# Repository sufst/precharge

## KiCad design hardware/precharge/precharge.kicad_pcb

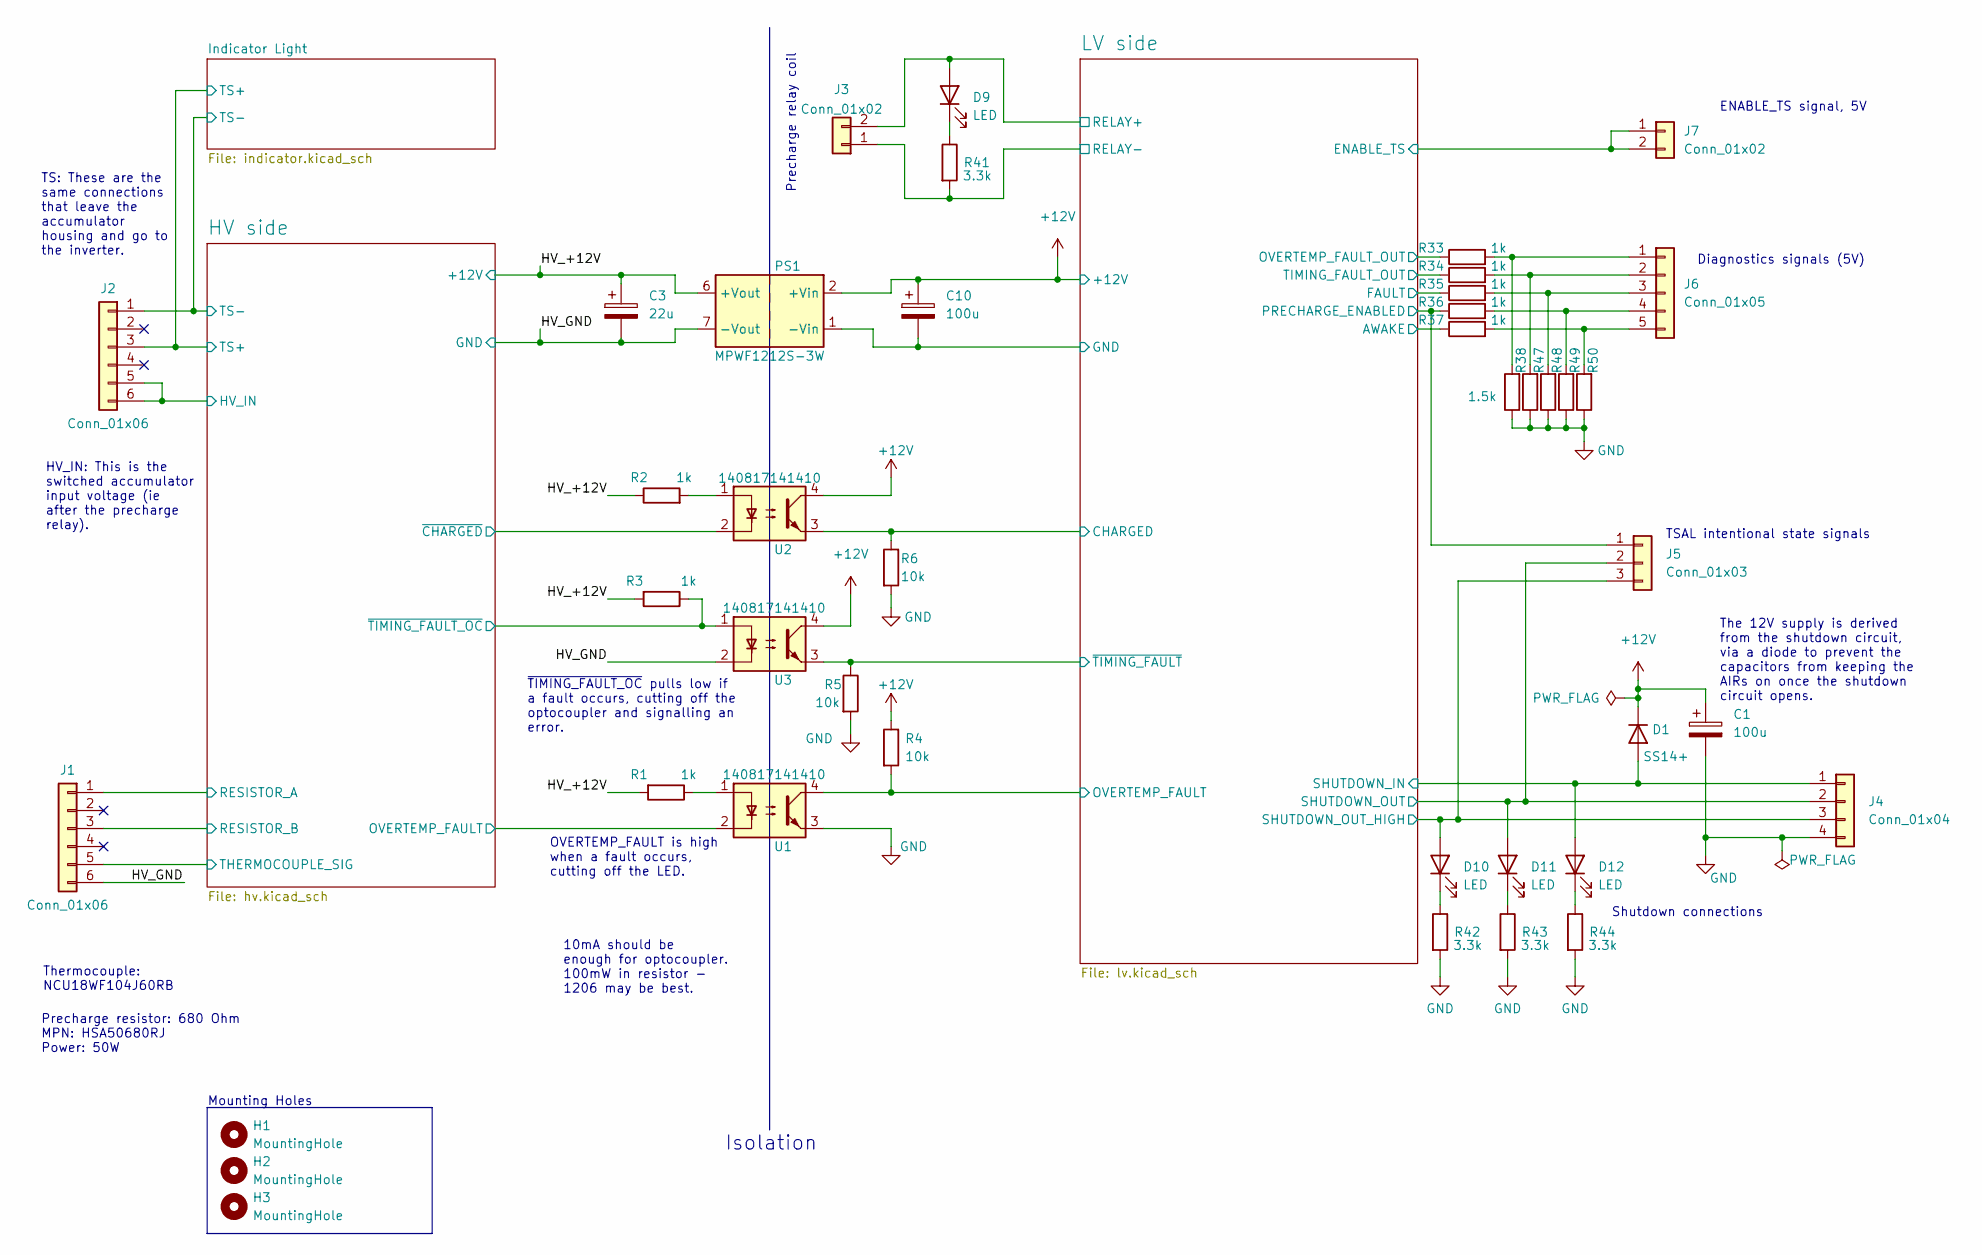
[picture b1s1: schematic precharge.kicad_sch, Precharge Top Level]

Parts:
C1, C10: 100u; CP_Radial_D6.3mm_P2.50mm
C3: 22u; CP_Radial_D8.0mm_P3.50mm
D1: SS14+; D_SMA
D9, D10, D11, D12: LED; LED_0603_1608Metric
H1, H2, H3: MountingHole; MountingHole_3.2mm_M3
J1, J2: Conn_01x06; Molex_Micro-Fit_3.0_43650-0600_1x06_P3.00mm_Horizontal
J3, J7: Conn_01x02; Molex_Micro-Fit_3.0_43650-0200_1x02_P3.00mm_Horizontal
J4: Conn_01x04; Molex_Micro-Fit_3.0_43650-0400_1x04_P3.00mm_Horizontal
J5: Conn_01x03; Molex_Micro-Fit_3.0_43650-0300_1x03_P3.00mm_Horizontal
J6: Conn_01x05; Molex_Micro-Fit_3.0_43650-0500_1x05_P3.00mm_Horizontal
PS1: MPWF1212S-3W
R1, R2, R3: 1k; R_1206_3216Metric
R4, R5, R6: 10k; R_0603_1608Metric
R33, R34, R35, R36, R37: 1k; R_0603_1608Metric
R38, R47, R48, R49, R50: 1.5k; R_0603_1608Metric
R41, R42, R43, R44: 3.3k; R_0603_1608Metric
U1, U2, U3: 140817141410; DIP-4_W10.16mm

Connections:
+12V: C1.1, C10.1, D1.1 (K), PS1.2 (+Vin), R4.1, U2.4, U3.4; also elsewhere on the board
/HV side/HV_IN: J2.5, J2.6; also elsewhere on the board
/HV side/OVERTEMP_FAULT: U1.2; also elsewhere on the board
/HV side/RESISTOR_A: J1.1; also elsewhere on the board
/HV side/RESISTOR_B: J1.3, J2.3; also elsewhere on the board
/HV side/THERMOCOUPLE_SIG: J1.5; also elsewhere on the board
/HV side/TS-: J2.1; also elsewhere on the board
/HV side/~CHARGED: U2.2; also elsewhere on the board
/HV side/~TIMING_FAULT_OC: R3.1, U3.1; also elsewhere on the board
/HV_+12V: C3.1, PS1.6 (+Vout), R1.2, R2.1, R3.2; also elsewhere on the board
/HV_GND: C3.2, J1.6, PS1.7 (-Vout), U3.2; also elsewhere on the board
/LV side/AWAKE: R37.1; also elsewhere on the board
/LV side/CHARGED: R6.1, U2.3; also elsewhere on the board
/LV side/ENABLE_TS: J7.1, J7.2; also elsewhere on the board
/LV side/FAULT: R35.1; also elsewhere on the board
/LV side/GND: C10.2, PS1.1 (-Vin); also elsewhere on the board
/LV side/OVERTEMP_FAULT: R4.2, U1.4; also elsewhere on the board
/LV side/OVERTEMP_FAULT_OUT: R33.1; also elsewhere on the board
/LV side/PRECHARGE_ENABLED: J5.1, R36.1; also elsewhere on the board
/LV side/RELAY+: D9.2 (A), J3.2; also elsewhere on the board
/LV side/RELAY-: J3.1, R41.2; also elsewhere on the board
/LV side/SHUTDOWN_IN: D1.2 (A), D12.2 (A), J4.1; also elsewhere on the board
/LV side/SHUTDOWN_OUT: D11.2 (A), J4.2, J5.2; also elsewhere on the board
/LV side/SHUTDOWN_OUT_HIGH: D10.2 (A), J4.3, J5.3; also elsewhere on the board
/LV side/TIMING_FAULT_OUT: R34.1; also elsewhere on the board
/LV side/~TIMING_FAULT: R5.1, U3.3; also elsewhere on the board
GND: C1.2, J4.4, R5.2, R6.2, R38.1, R42.2, R43.2, R44.2, R47.1, R48.1, R49.1, R50.1, U1.3
unnamed: D9.1 (K), R41.1
unnamed: D10.1 (K), R42.1
unnamed: D11.1 (K), R43.1
unnamed: D12.1 (K), R44.1
unnamed: J6.1, R33.2, R38.2
unnamed: J6.2, R34.2, R47.2
unnamed: J6.3, R35.2, R48.2
unnamed: J6.4, R36.2, R49.2
unnamed: J6.5, R37.2, R50.2
unnamed: R1.1, U1.1
unnamed: R2.2, U2.1

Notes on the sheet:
10mA should be enough for optocoupler. 100mW in resistor - 1206 may be best.
Diagnostics signals (5V)
OVERTEMP_FAULT is high when a fault occurs, cutting off the LED.
Isolation
~{TIMING_FAULT_OC} pulls low if a fault occurs, cutting off the optocoupler and signalling an error.
Precharge relay coil
ENABLE_TS signal, 5V
Shutdown connections
Thermocouple: NCU18WF104J60RB
Mounting Holes
TS: These are the same connections that leave the accumulator housing and go to the inverter.
HV_IN: This is the switched accumulator input voltage (ie after the precharge relay).
Precharge resistor: 680 Ohm MPN: HSA50680RJ Power: 50W
TSAL intentional state signals
The 12V supply is derived from the shutdown circuit, via a diode to prevent the capacitors from keeping the AIRs on once the shutdown circuit opens.

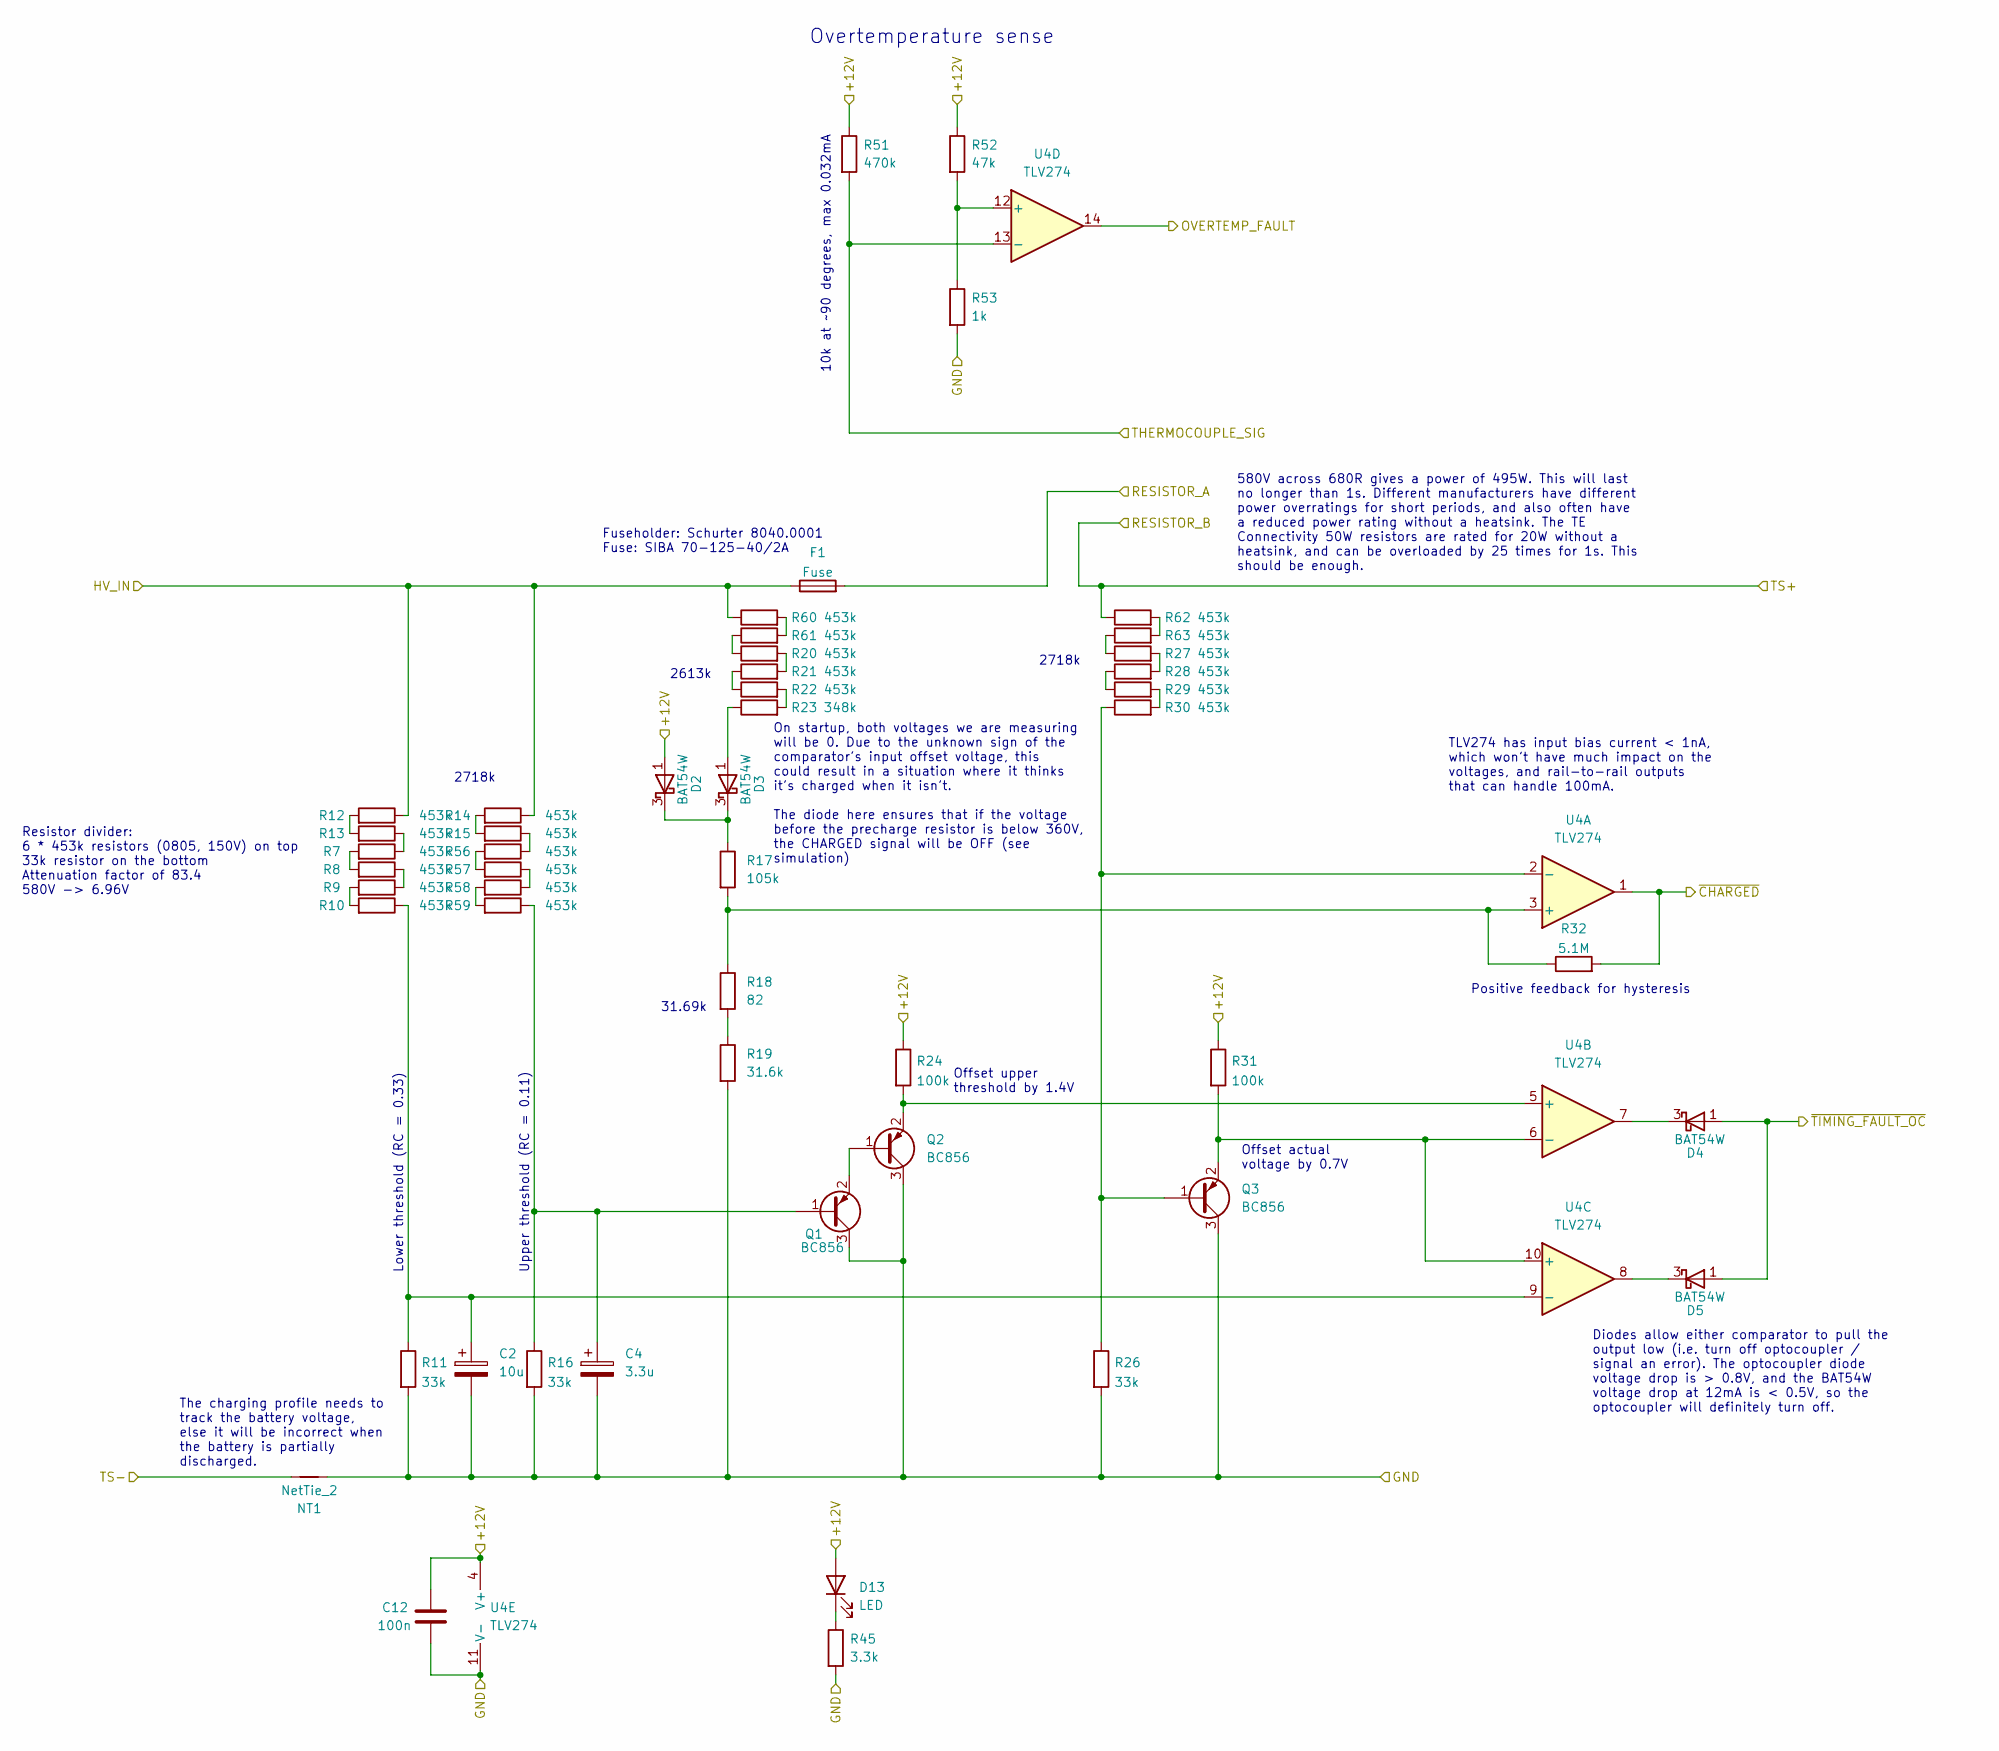
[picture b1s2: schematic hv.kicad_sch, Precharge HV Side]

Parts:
C2: 10u; CP_Radial_D5.0mm_P2.00mm
C4: 3.3u; CP_Radial_D5.0mm_P2.00mm
C12: 100n; C_0603_1608Metric
D2, D3, D4, D5: BAT54W; SOT-323_SC-70
D13: LED; LED_0603_1608Metric
F1: Fuse; fuseholder
NT1: NetTie_2; NetTie-2_SMD_Pad0.5mm
Q1, Q2, Q3: BC856; SOT-23
R7, R8, R9, R10, R12, R13, R14, R15, R20, R21, R22, R27, R28, R29, R30, R56, R57, R58, R59, R60, R61, R62, R63: 453k; R_0805_2012Metric
R11, R16, R26: 33k; R_0603_1608Metric
R17: 105k; R_0805_2012Metric
R18: 82; R_0603_1608Metric
R19: 31.6k; R_0603_1608Metric
R23: 348k; R_0805_2012Metric
R24, R31: 100k; R_0603_1608Metric
R32: 5.1M; R_0603_1608Metric
R45: 3.3k; R_0603_1608Metric
R51: 470k; R_0603_1608Metric
R52: 47k; R_0603_1608Metric
R53: 1k; R_0603_1608Metric
U4: TLV274; SOIC-14_3.9x8.7mm_P1.27mm

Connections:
/HV side/HV_IN: F1.1, R12.1, R14.1, R60.1; also elsewhere on the board
/HV side/OVERTEMP_FAULT: U4.14; also elsewhere on the board
/HV side/RESISTOR_A: F1.2; also elsewhere on the board
/HV side/RESISTOR_B: R62.1; also elsewhere on the board
/HV side/THERMOCOUPLE_SIG: R51.2, U4.13 (-); also elsewhere on the board
/HV side/TS-: NT1.2; also elsewhere on the board
/HV side/~CHARGED: R32.2, U4.1; also elsewhere on the board
/HV side/~TIMING_FAULT_OC: D4.1 (A), D5.1 (A); also elsewhere on the board
/HV_+12V: C12.1, D2.1 (A), D13.2 (A), R24.1, R31.1, R51.1, R52.1, U4.4 (V+); also elsewhere on the board
/HV_GND: C2.2, C4.2, C12.2, NT1.1, Q1.3 (C), Q2.3 (C), Q3.3 (C), R11.2, R16.2, R19.2, R26.2, R45.2, R53.2, U4.11 (V-); also elsewhere on the board
unnamed: C2.1, R10.1, R11.1, U4.9 (-)
unnamed: C4.1, Q1.1 (B), R16.1, R59.1
unnamed: D2.3 (K), D3.3 (K), R17.1
unnamed: D3.1 (A), R23.1
unnamed: D4.3 (K), U4.7
unnamed: D5.3 (K), U4.8
unnamed: D13.1 (K), R45.1
unnamed: Q1.2 (E), Q2.1 (B)
unnamed: Q2.2 (E), R24.2, U4.5 (+)
unnamed: Q3.1 (B), R26.1, R30.1, U4.2 (-)
unnamed: Q3.2 (E), R31.2, U4.6 (-), U4.10 (+)
unnamed: R7.2, R8.2
unnamed: R8.1, R9.1
unnamed: R9.2, R10.2
unnamed: R12.2, R13.2
unnamed: R7.1, R13.1
unnamed: R14.2, R15.2
unnamed: R15.1, R56.1
unnamed: R17.2, R18.1, R32.1, U4.3 (+)
unnamed: R18.2, R19.1
unnamed: R20.1, R61.1
unnamed: R20.2, R21.2
unnamed: R21.1, R22.1
unnamed: R22.2, R23.2
unnamed: R27.1, R63.1
unnamed: R27.2, R28.2
unnamed: R28.1, R29.1
unnamed: R29.2, R30.2
unnamed: R52.2, R53.1, U4.12 (+)
unnamed: R56.2, R57.2
unnamed: R57.1, R58.1
unnamed: R58.2, R59.2
unnamed: R60.2, R61.2
unnamed: R62.2, R63.2

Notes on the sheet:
Resistor divider: 6 * 453k resistors (0805, 150V) on top 33k resistor on the bottom Attenuation factor of 83.4 580V -> 6.96V
On startup, both voltages we are measuring will be 0. Due to the unknown sign of the comparator's input offset voltage, this could result in a situation where it thinks it's charged when it isn't. The diode here ensures that if the voltage before the precharge resistor is below 360V, the CHARGED si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
Diodes allow either comparator to pull the output low (i.e. turn off optocoupler / signal an error). The optocoupler diode voltage drop is > 0.8V, and the BAT54W voltage drop at 12mA is < 0.5V, so the optocoupler will definitely turn off.
Overtemperature sense
TLV274 has input bias current < 1nA, which won't have much impact on the voltages, and rail-to-rail outputs that can handle 100mA.
31.69k
Offset actual voltage by 0.7V
2718k
Fuseholder: Schurter 8040.0001 Fuse: SIBA 70-125-40/2A
Upper threshold (RC = 0.11)
Lower threshold (RC = 0.33)
Offset upper threshold by 1.4V
The charging profile needs to track the battery voltage, else it will be incorrect when the battery is partially discharged.
580V across 680R gives a power of 495W. This will last no longer than 1s. Different manufacturers have different power overratings for short periods, and also often have a reduced power rating without a heatsink. The TE Connectivity 50W resistors are rated for 20W without a heatsink, and can be ove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
2613k
10k at ~90 degrees, max 0.032mA
Positive feedback for hysteresis

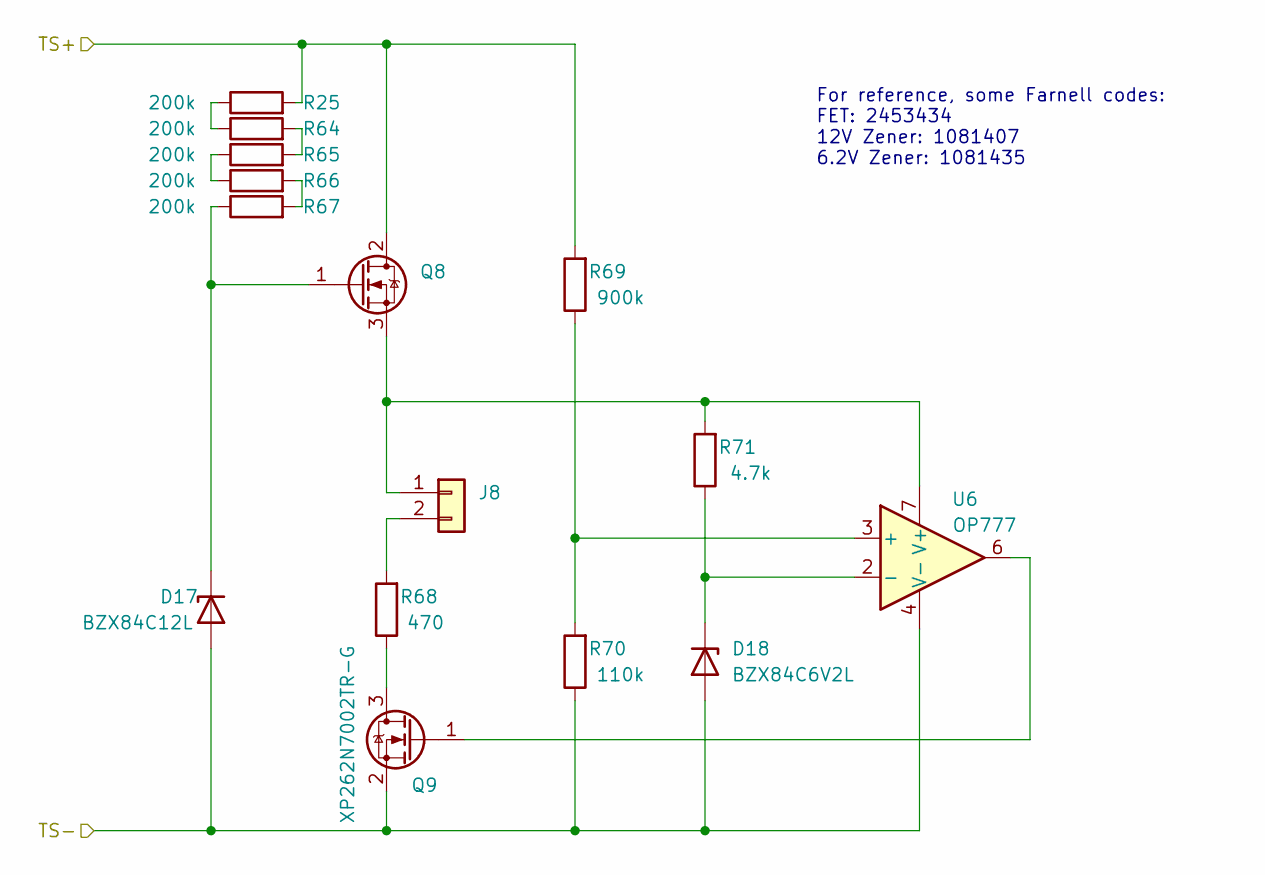
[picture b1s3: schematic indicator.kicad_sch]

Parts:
D17: BZX84C12L; SOT-23
D18: BZX84C6V2L; SOT-23
J8: (no value)
Q8: (no value)
Q9: XP262N7002TR-G; SOT-23
R25, R64, R65, R66, R67: 200k; R_0805_2012Metric
R68: 470; R_0603_1608Metric
R69: 900k; R_0603_1608Metric
R70: 110k; R_0603_1608Metric
R71: 4.7k; R_0603_1608Metric
U6: OP777; SOIC-8_3.9x4.9mm_P1.27mm

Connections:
/Indicator Light/TS+: Q8.2 (D), R25.2, R69.2
/Indicator Light/TS-: D17.1 (A), D18.1 (A), Q9.2 (S), R70.1, U6.4 (V-)
unnamed: D17.3 (K), Q8.1 (G), R67.1
unnamed: D18.3 (K), R71.1, U6.2 (-)
unnamed: J8.1, Q8.3 (S), R71.2, U6.7 (V+)
unnamed: J8.2, R68.2
unnamed: Q9.1 (G), U6.6
unnamed: Q9.3 (D), R68.1
unnamed: R25.1, R64.1
unnamed: R64.2, R65.2
unnamed: R65.1, R66.1
unnamed: R66.2, R67.2
unnamed: R69.1, R70.2, U6.3 (+)

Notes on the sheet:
For reference, some Farnell codes: FET: 2453434 12V Zener: 1081407 6.2V Zener: 1081435

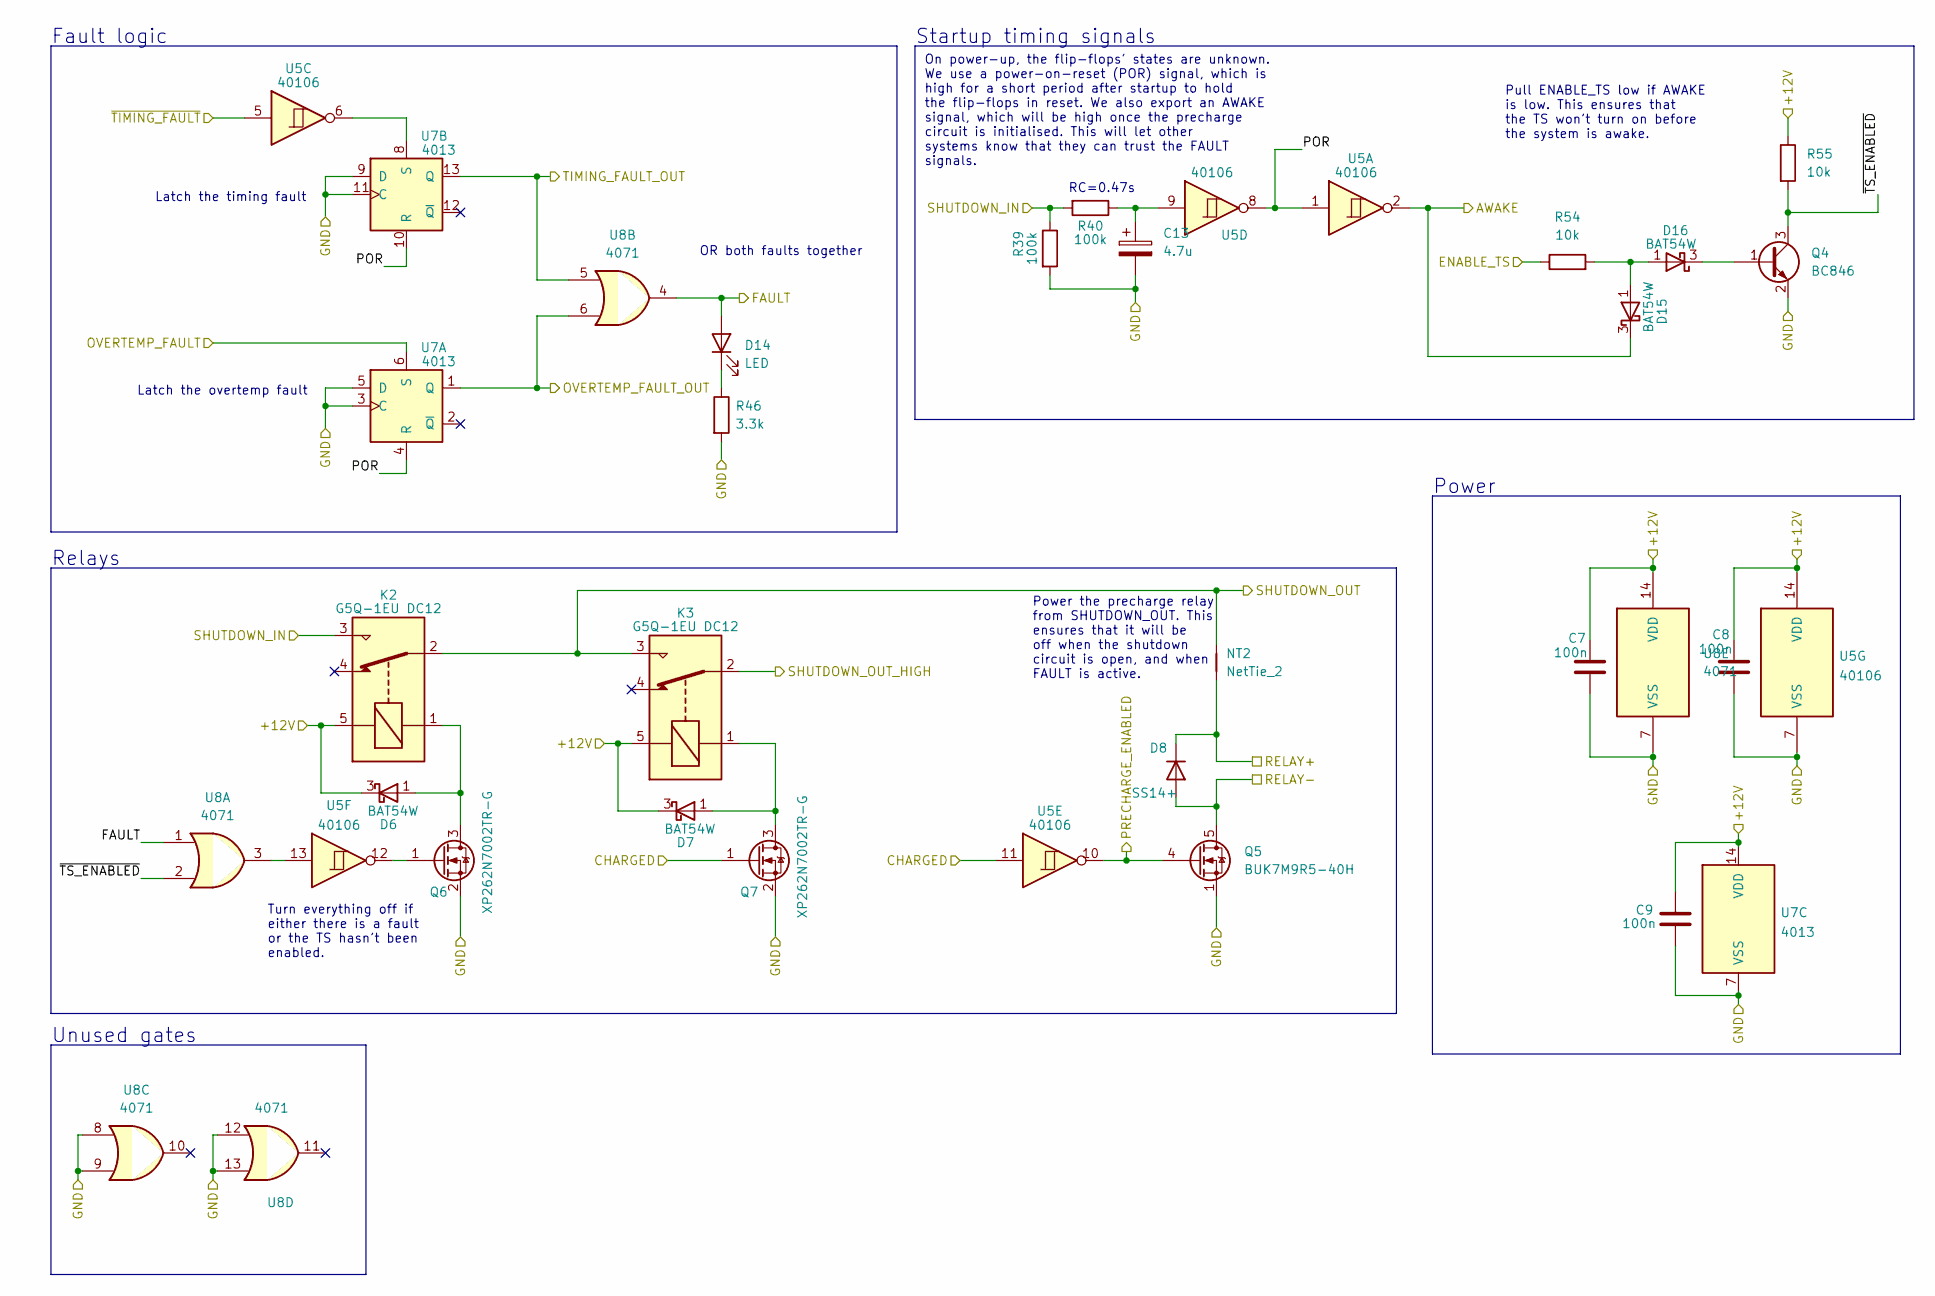
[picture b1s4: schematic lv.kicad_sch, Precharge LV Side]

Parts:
C7, C8, C9: 100n; C_0603_1608Metric
C13: 4.7u; CP_Radial_D5.0mm_P2.00mm
D6, D7, D15, D16: BAT54W; SOT-323_SC-70
D8: SS14+; D_SMA
D14: LED; LED_0603_1608Metric
K2, K3: G5Q-1EU DC12; PCH-112L2MH
NT2: NetTie_2; NetTie-2_SMD_Pad0.5mm
Q4: BC846; SOT-23
Q5: BUK7M9R5-40H; LFPAK33
Q6, Q7: XP262N7002TR-G; SOT-23
R39, R40: 100k; R_0603_1608Metric
R46: 3.3k; R_0603_1608Metric
R54, R55: 10k; R_0603_1608Metric
U5: 40106; SOIC-14_3.9x8.7mm_P1.27mm
U7: 4013; SOIC-14_3.9x8.7mm_P1.27mm
U8: 4071; SOIC-14_3.9x8.7mm_P1.27mm

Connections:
+12V: C7.1, C8.1, C9.1, D6.3 (K), D7.3 (K), K2.5, K3.5, R55.1, U5.14 (VDD), U7.14 (VDD), U8.14 (VDD); also elsewhere on the board
/LV side/AWAKE: D15.3 (K), U5.2; also elsewhere on the board
/LV side/CHARGED: Q7.1 (G), U5.11; also elsewhere on the board
/LV side/ENABLE_TS: R54.1; also elsewhere on the board
/LV side/FAULT: D14.2 (A), U8.1, U8.4; also elsewhere on the board
/LV side/GND: C7.2, C8.2, C9.2, C13.2, Q4.2 (E), Q5.1 (S), Q5.2 (S), Q5.3 (S), Q6.2 (S), Q7.2 (S), R39.2, R46.2, U5.7 (VSS), U7.3 (C), U7.5 (D), U7.7 (VSS), U7.9 (D), U7.11 (C), U8.7 (VSS), U8.8, U8.9, U8.12, U8.13; also elsewhere on the board
/LV side/OVERTEMP_FAULT: U7.6 (S); also elsewhere on the board
/LV side/OVERTEMP_FAULT_OUT: U7.1 (Q), U8.6; also elsewhere on the board
/LV side/POR: U5.1, U5.8, U7.4 (R), U7.10 (R)
/LV side/PRECHARGE_ENABLED: Q5.4 (G), U5.10; also elsewhere on the board
/LV side/RELAY+: D8.1 (K), NT2.1; also elsewhere on the board
/LV side/RELAY-: D8.2 (A), Q5.5 (D); also elsewhere on the board
/LV side/SHUTDOWN_IN: K2.3, R39.1, R40.2; also elsewhere on the board
/LV side/SHUTDOWN_OUT: K2.2, K3.3, NT2.2; also elsewhere on the board
/LV side/SHUTDOWN_OUT_HIGH: K3.2; also elsewhere on the board
/LV side/TIMING_FAULT_OUT: U7.13 (Q), U8.5; also elsewhere on the board
/LV side/~TIMING_FAULT: U5.5; also elsewhere on the board
/LV side/~TS_ENABLED: Q4.3 (C), R55.2, U8.2
unnamed: C13.1, R40.1, U5.9
unnamed: D6.1 (A), K2.1, Q6.3 (D)
unnamed: D7.1 (A), K3.1, Q7.3 (D)
unnamed: D14.1 (K), R46.1
unnamed: D15.1 (A), D16.1 (A), R54.2
unnamed: D16.3 (K), Q4.1 (B)
unnamed: Q6.1 (G), U5.12
unnamed: U5.6, U7.8 (S)
unnamed: U5.13, U8.3

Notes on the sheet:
Latch the timing fault
Startup timing signals
Latch the overtemp fault
Power
On power-up, the flip-flops' states are unknown. We use a power-on-reset (POR) signal, which is high for a short period after startup to hold the flip-flops in reset. We also export an AWAKE signal, which will be high once the precharge circuit is initialised. This will let other systems know that 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
Power the precharge relay from SHUTDOWN_OUT. This ensures that it will be off when the shutdown circuit is open, and when FAULT is active.
Turn everything off if either there is a fault or the TS hasn't been enabled.
Fault logic
Pull ENABLE_TS low if AWAKE is low. This ensures that the TS won't turn on before the system is awake.
OR both faults together
RC=0.47s
Unused gates
Relays

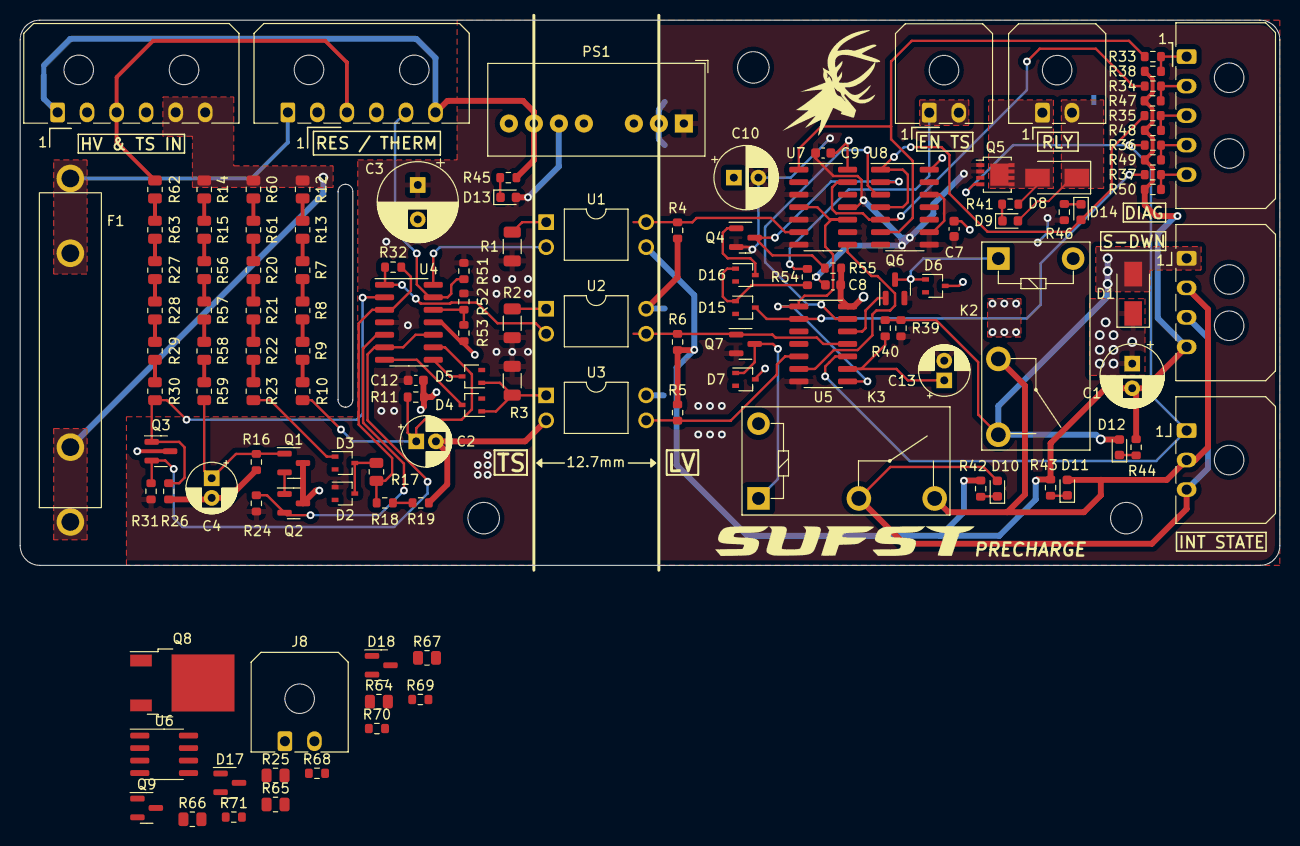
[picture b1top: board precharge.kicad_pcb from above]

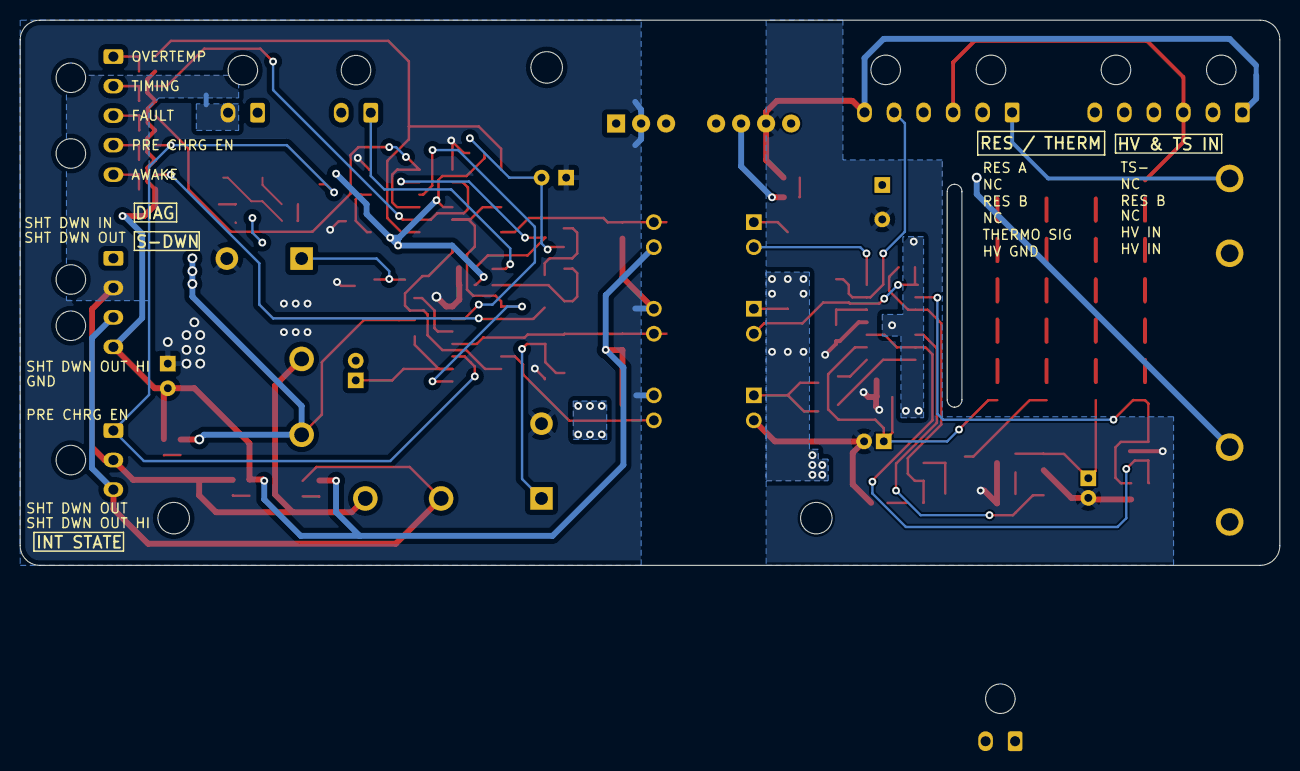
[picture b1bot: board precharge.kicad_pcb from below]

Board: 2 copper layers, 128.0 x 55.4 mm, 133 parts (2 on the bottom side), 96 nets.

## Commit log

2021-08-29 Added library as submodule
2021-08-29 Added Kicad project
2021-08-29 Updated symbol library
2021-08-29 Updated symbol library path
2021-08-29 Added test symbol to schematic
2021-08-29 Added charge envelope sheet
2021-08-29 update gitignore
2021-08-29 add basic LTSpice simulation of inverter precharge
2021-10-29 Made very rough outline of the precharge/discharge circuit. Probably wrong...
2021-10-29 Deleted unused files
    I think the new version of Kicad is using different file extensions,
    so some of the old files are unused.
2021-11-09 The precharge needs to be inside the accumulator housing
2021-11-10 Add circuitry to make use of the inverter's analogue inputs and relay outputs
2021-11-20 Moved outline into a separate directory and created precharge project with just precharge circuitry
2021-11-29 Misc. changes to schematic, created PCB
    The PCB was created just to begin modelling its size.
2021-12-06 Modifications to outline schematic
2021-12-06 Deleting outline because it is no longer up to date.
    I currently have no intention of updating the outline. If someone really
    wants it, feel free to bring it back.
2021-12-06 Major changes to schematic
    - Split into HV and LV sections
    - Implemented most of the precharge logic
2021-12-07 Tweaks made during today's meeting
2022-01-06 Updated quite a bit
    - Added relay mechanical state detection
    - Selected most component values for HV side
    - Other miscellaneous changes
2022-01-06 Added simulation of voltage levels for charge and profile detection.
    In LTSpice, run the simulation, then click on the plot window. In the
    menu bar, select "Plot settings" and load either the
    "charge_measurement.plt" plot settings file, or the "profile.plt"
    file.
2022-01-06 Added python script for hysteresis calculations
2022-01-09 Added part numbers for most components, added LEDs, tweaked LV side.
2022-01-19 Tweaks, nearly done
2022-02-02 Assigned some footprints, created footprint library
2022-02-04 Preliminary PCB placement
2022-02-04 Initial BOM
2022-02-16 Added support for TS_ACTIVE signal, adjusted resistor divider
2022-02-16 Added footprints
2022-02-20 Restarted PCB layout
2022-04-21 Added precharge layout
2022-05-15 Added initial indicator light
2022-10-03 Latest precharge updates
